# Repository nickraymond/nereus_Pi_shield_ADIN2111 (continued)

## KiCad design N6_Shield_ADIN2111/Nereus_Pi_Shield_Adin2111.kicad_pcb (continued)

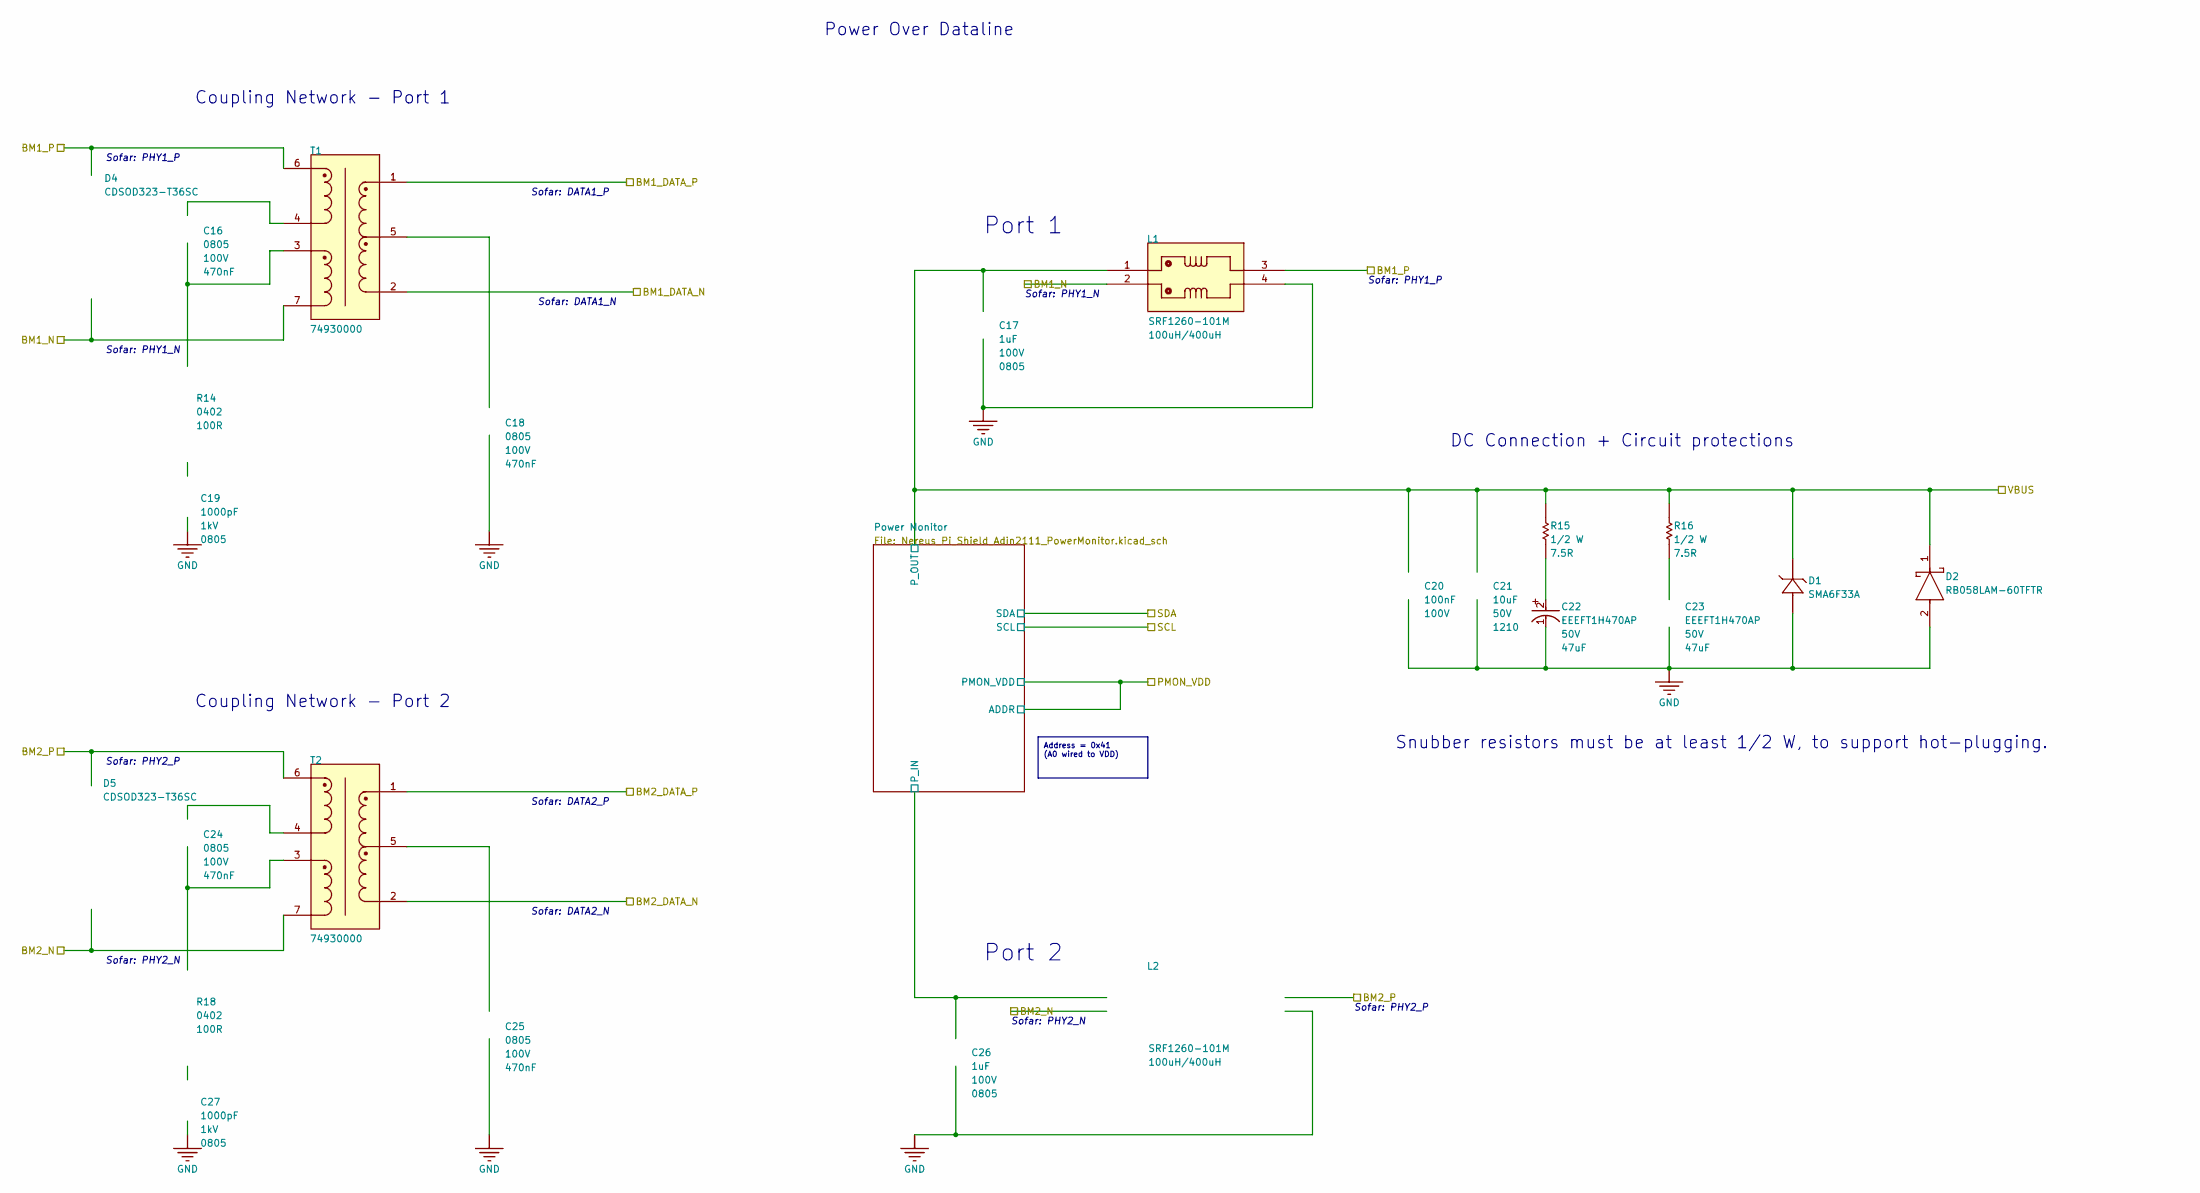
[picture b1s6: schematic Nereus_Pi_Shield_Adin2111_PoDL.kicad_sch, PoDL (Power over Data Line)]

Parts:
C16, C18, C24, C25: 08051C474KAT2A; FP-0805-L_2_01_0_2-W_1_25-MFG; TOLERANCE 10%; VOLTAGE RATING 100V
C17, C26: C2012X7S2A105K125AB; FP-C2012-125-0_2-MFG; VOLTAGE RATING (DC) 100V; VOLTAGE 100V
C19, C27: C0805C102MDRACTU; CAPC2013X145X50LL20T25; VOLTAGE 1kV; PART NUMBER C0805C102MDRACTU
C20: GRM188R72A104KA35D; FP-GRM188-0_1-e0_2_0_5-IPC_B; VOLTAGE RATING (DC) 100V; VOLTAGE 100V
C21: CL32B106KBJNNNE; FP-CL32-IPC_C; VOLTAGE RATING (DC) 50V; VOLTAGE RATING 50V
C22, C23: EEEFT1H470AP; FP-FTD-MFG; VOLTAGE 50V; TOLERANCE 20%
D1: SMA6F33A; SMA6F33A-Footprint-1; VOLTAGE - CLAMPING (MAX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 53.1V; VOLTAGE - REVERSE STAND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 33V; MANUFACTURERPARTNUMBER1 SMA6F33A-M3/H
D2: RB058LAM-60TFTR; FP-PMDTM-MFG
D4, D5: CDSOD323-T36SC; FP-SOD-323-MFG; BREAKDOWN VOLTAGE 40V; CLAMPING VOLTAGE 75V; MANUFACTURER PART NUMBER CDSOD323-T36SC; DIGIKEY DESCRIPTION TVS DIODE 36V 75V SOD323
L1, L2: SRF1260-101M; SRF1260-101M-Footprint-1
R14, R18: RR0510P-101-D; FP-RR0510-IPC_B; RESISTANCE TOLERANCE 0.5%; POWER RATING 63mW
R15, R16: CRCW08057R50FKEAHP; CRCW08057R50FKEAHP-Footprint-1; MANUFACTURERPARTNUMBER CRCW08057R50FKEAHP
T1, T2: 74930000; FP-74930000-MFG

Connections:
/Top-Level Schematic/BM1_DATA_N: T1.2; also elsewhere on the board
/Top-Level Schematic/BM1_DATA_P: T1.1; also elsewhere on the board
/Top-Level Schematic/BM1_N: D4.2, L1.2, T1.7; also elsewhere on the board
/Top-Level Schematic/BM1_P: D4.1, L1.3, T1.6; also elsewhere on the board
/Top-Level Schematic/BM2_DATA_N: T2.2; also elsewhere on the board
/Top-Level Schematic/BM2_DATA_P: T2.1; also elsewhere on the board
/Top-Level Schematic/BM2_N: D5.2, L2.2, T2.7; also elsewhere on the board
/Top-Level Schematic/BM2_P: D5.1, L2.3, T2.6; also elsewhere on the board
/Top-Level Schematic/PoDL/Power Monitor/P_IN: C26.1, L2.1; also elsewhere on the board
GND: C17.2, C18.1, C19.1, C20.2, C21.2, C22.1 (C), C23.1 (C), C25.1, C26.2, C27.1, D1.1 (ANODE), D2.2 (A), L1.4, L2.4; also elsewhere on the board
unnamed: C16.1, R14.1, T1.3
unnamed: C16.2, T1.4
unnamed: C18.2, T1.5
unnamed: C19.2, R14.2
unnamed: C22.2 (A), R15.1
unnamed: C23.2 (A), R16.1
unnamed: C24.1, R18.1, T2.3
unnamed: C24.2, T2.4
unnamed: C25.2, T2.5
unnamed: C27.2, R18.2
VBUS: C17.1, C20.1, C21.1, D1.2 (CATHODE), D2.1 (C), L1.1, R15.2, R16.2; also elsewhere on the board

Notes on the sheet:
Coupling Network - Port 2
DC Connection + Circuit protections
Sofar: PHY1_P
Sofar: PHY1_N
Sofar: DATA1_P
Snubber resistors must be at least 1/2 W, to support hot-plugging.
Port 2
Coupling Network - Port 1
Sofar: PHY2_P
Sofar: DATA1_N
Port 1
Sofar: DATA2_N
Sofar: DATA2_P
Sofar: PHY2_N
Address = 0x41 (A0 wired to VDD)
Power Over Dataline

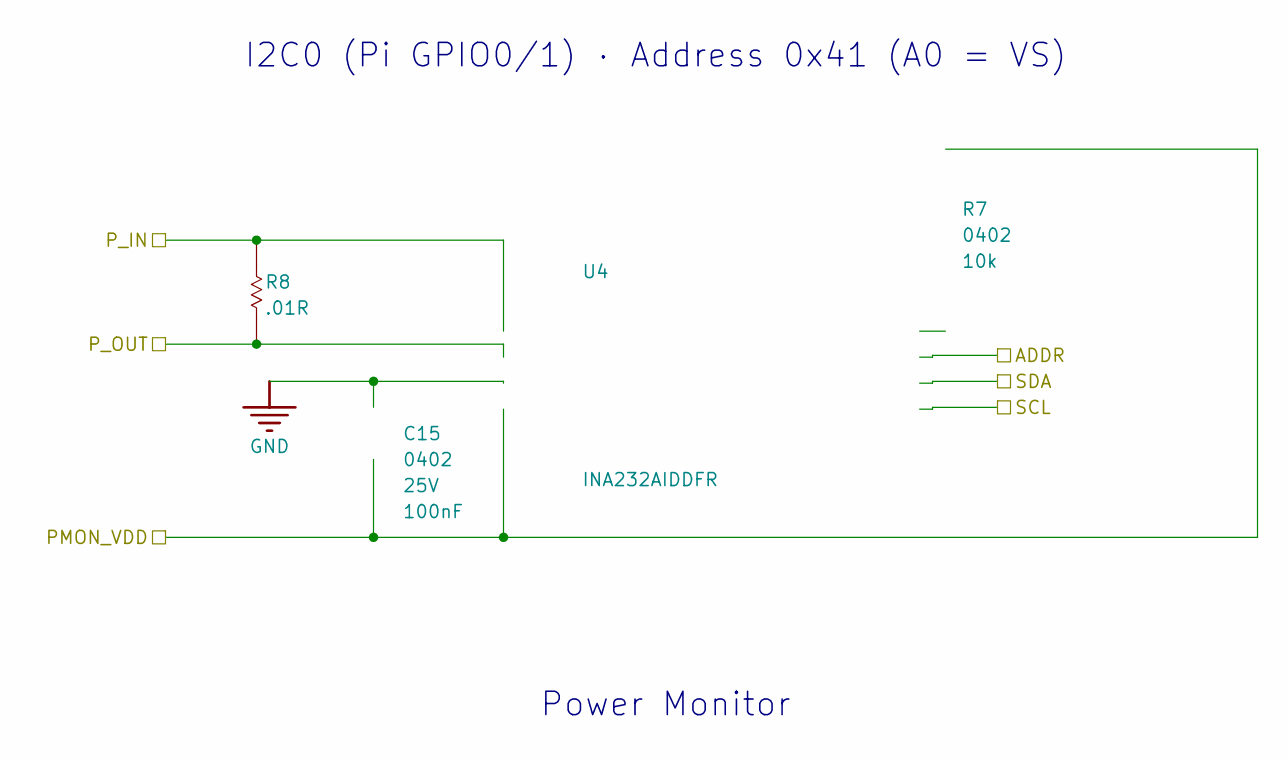
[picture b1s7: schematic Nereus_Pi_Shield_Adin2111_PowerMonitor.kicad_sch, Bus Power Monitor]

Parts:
C15: CL05A104KA5NNNC; FP-CL278-IPC_C; VOLTAGE 25V; VOLTAGE RATING 25V
R7: RC0402JR-0710KL; FP-RC0402-0_4-IPC_C; RESISTANCE TOLERANCE 5%; POWER RATING 62.5mW
R8: UR73D1JTTD10L0F; RESC1608X60X55ML20T10; MANUFACTURERPARTNUMBER UR73D1JTTD10L0F
U4: INA232AIDDFR; INA232AIDDFR-Footprint-1

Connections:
3V3: C15.2, R7.1, U4.4 (VS), U4.7 (A0); also elsewhere on the board
/Top-Level Schematic/I2C0_SCL: U4.5 (SCL); also elsewhere on the board
/Top-Level Schematic/I2C0_SDA: U4.6 (SDA); also elsewhere on the board
/Top-Level Schematic/PoDL/Power Monitor/P_IN: R8.2, U4.1 (IN+); also elsewhere on the board
GND: C15.1, U4.3 (GND); also elsewhere on the board
unnamed: R7.2, U4.8 (ALERT)
VBUS: R8.1, U4.2 (IN-); also elsewhere on the board

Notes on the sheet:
I2C0 (Pi GPIO0/1) · Address 0x41 (A0 = VS)
Power Monitor

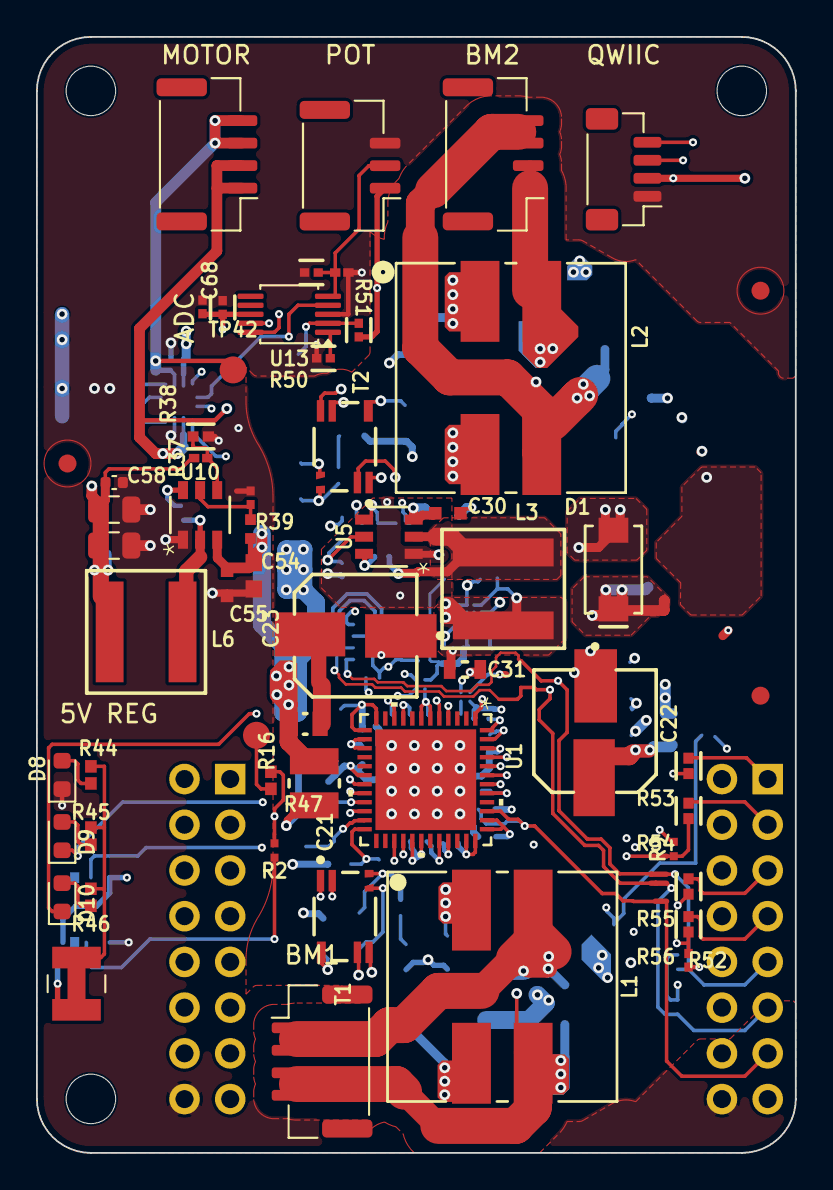
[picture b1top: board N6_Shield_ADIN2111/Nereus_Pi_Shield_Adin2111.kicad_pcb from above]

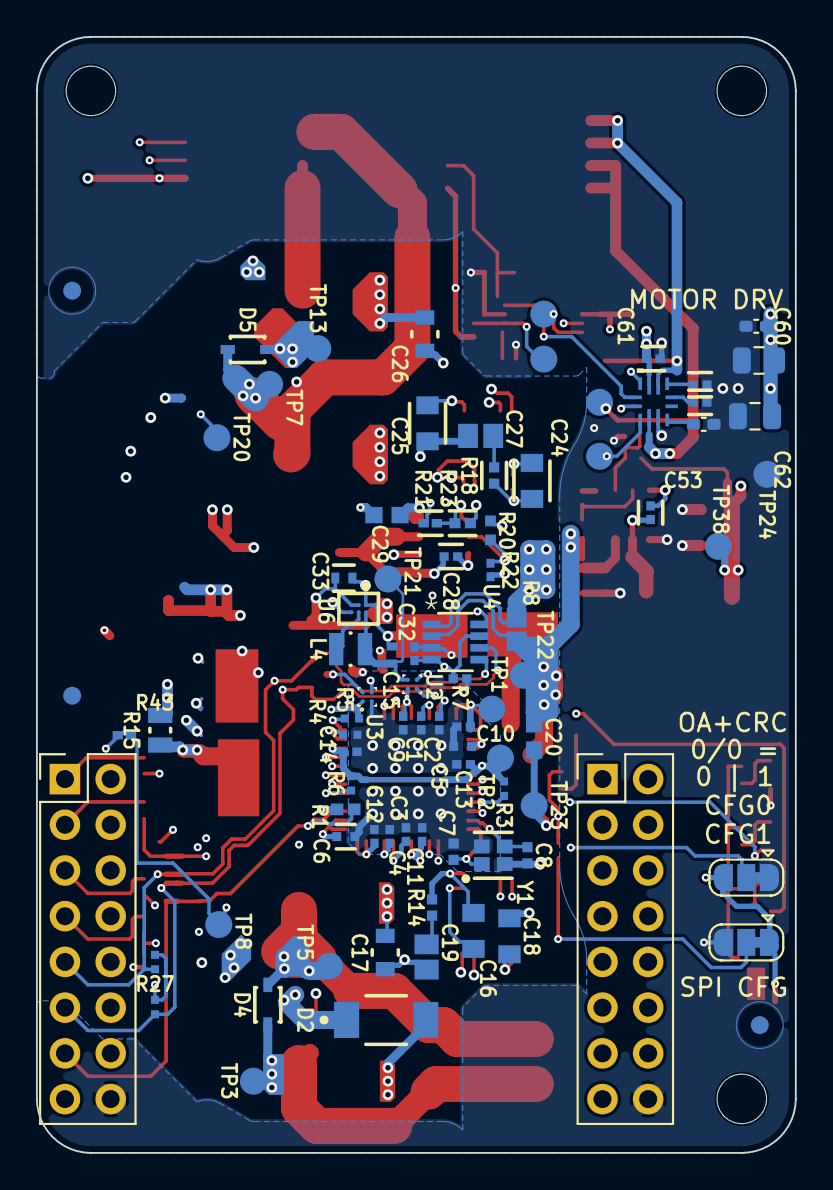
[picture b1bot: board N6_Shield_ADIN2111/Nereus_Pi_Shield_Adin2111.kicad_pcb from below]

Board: 6 copper layers, 42.2 x 62.0 mm, 147 parts (87 on the bottom side), 83 nets.

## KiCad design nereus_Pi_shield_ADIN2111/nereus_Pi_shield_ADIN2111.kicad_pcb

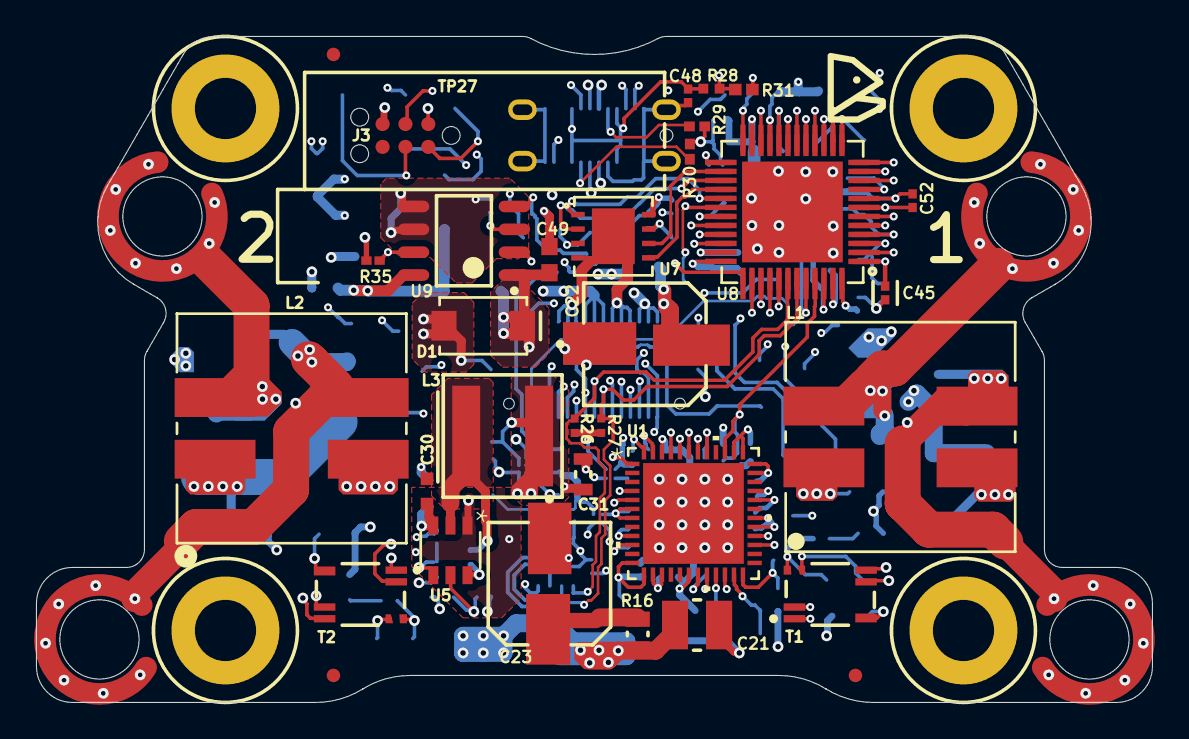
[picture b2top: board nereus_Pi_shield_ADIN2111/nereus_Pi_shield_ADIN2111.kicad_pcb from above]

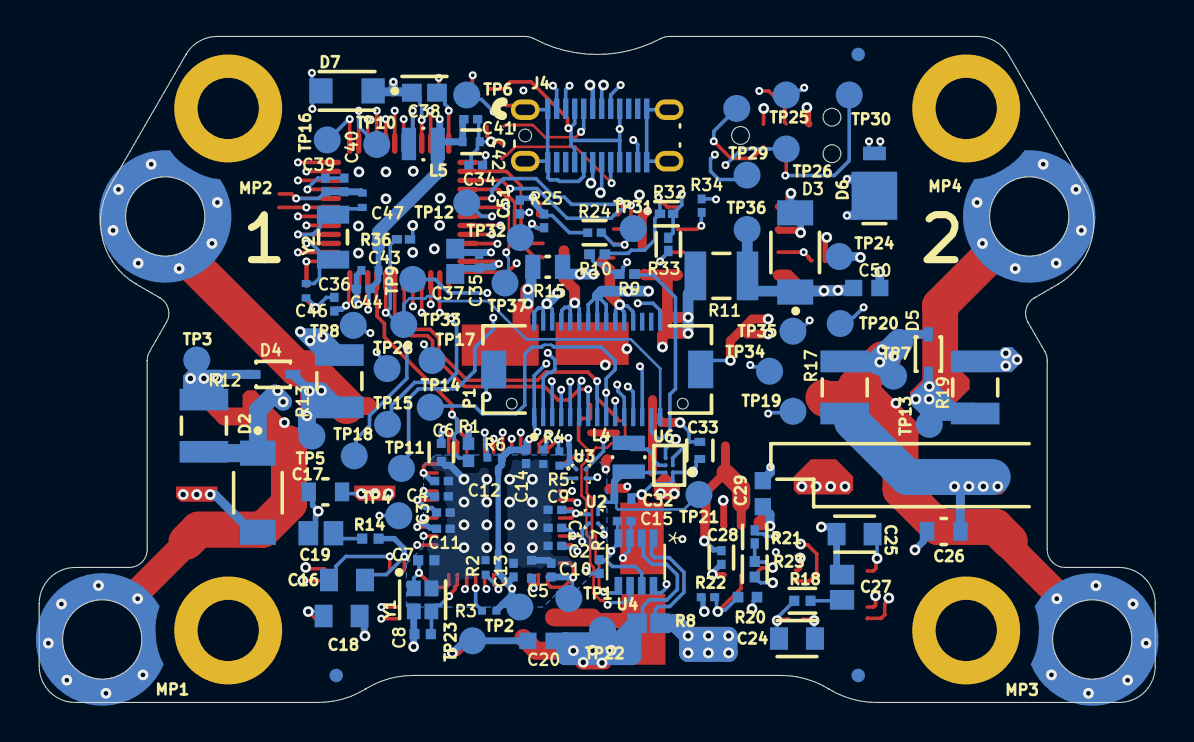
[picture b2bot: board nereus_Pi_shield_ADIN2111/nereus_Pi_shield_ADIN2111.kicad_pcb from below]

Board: 6 copper layers, 62.0 x 37.0 mm, 167 parts (131 on the bottom side), 92 nets.

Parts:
C1, C3, C9, C10, C11, C12, C13, C14, C15, C28, C34, C35, C36, C39, C41, C44, C45, C48, C51, C52: CL05A104KA5NNNC; FP-CL278-IPC_C
C2, C4, C40: CL05A105KP5NNNC; FP-CL511-IPC_C
C5, C6: CC0402KRX5R6BB684; FP-CC0402-MFG
C7, C8: CC0402JRNPO9BN150; FP-CC0402-0_55-IPC_B
C16, C18, C24, C25: 08051C474KAT2A; FP-0805-L_2_01_0_2-W_1_25-MFG
C17, C26: C2012X7S2A105K125AB; FP-C2012-125-0_2-MFG
C19, C27: C0805C102MDRACTU; CAPC2013X145X50LL20T25
C20, C29, C49, C50: GRM188R72A104KA35D; FP-GRM188-0_1-e0_2_0_5-IPC_B
C21: CL32B106KBJNNNE; FP-CL32-IPC_C
C22, C23: EEEFT1H470AP; FP-FTD-MFG
C30: UMK107BBJ225KA-T; FP-0603-L_1_6_0_2-W_0_8_0-MFG
C31: C1608X5R0J226M080AC; CAPC1608X100X20ML10
C32: GRJ155R60J106ME11D; FP-GRJ155-0_2-MFG
C33: GRM155R60J475ME87D; FP-GRM155-0_15-MFG
C37, C38: GRM188D71A106MA73D; FP-GRM188-0_2-IPC_B
C42, C43: LMK105BJ225KV-F; FP-0402-L_1_0_0_05-W_0_5-MFG
C46, C47: CGA2B2C0G1H050C050BA; FP-CGA2B-MFG
D1: SMA6F33A; SMA6F33A-Footprint-1
D2, D3: RB058LAM-60TFTR; FP-PMDTM-MFG
D4, D5: CDSOD323-T36SC; FP-SOD-323-MFG
D6: SS3P3-M3/84A; SS3P3-M3_84A-Footprint-1
D7: SMF3.3; FP-SMF3_3-MFG
FID1, FID2, FID3, FID4, FID5, FID6: FIDUCIAL; FIDUCIAL_075MM
J3: TC2030-FP-sofar; TC2030-FP-Footprint-1
J4: USB4160-03-0070-C; USB4160-03-0070-C-Footprint-1
L1, L2: SRF1260-101M; SRF1260-101M-Footprint-1
L3: PA5432.822NLT; FP-PA5432_472NLT-MFG
L4: DFE201612E-2R2M=P2; FP-DFE201612C-MFG
L5: LQM2MPN2R2NG0L; FP-LQM2MPN_G0-MFG
MP1, MP2, MP3, MP4: 78614015360; 78614015360-Footprint-2
MTG1, MTG2, MTG3, MTG4: Hole_M3
P1: DF17(3.0)-30DS-0.5V(57); FP-DF17_3_0H_-30DS-0_5V_5-MFG
R1, R31: RC0402FR-071K5L; RESC1005X40X25ML05T10
R2, R3, R4, R5, R6, R26, R27: ERJ-2RKF4701X; RESC1005X40X25LL05T05
R7, R24, R25: RC0402JR-0710KL; FP-RC0402-0_4-IPC_C
R8: UR73D1JTTD10L0F; RESC1608X60X55ML20T10
R9, R10: RC0402JR-070RL; RESC1005X40X25NL05T10
R11, R12, R13, R17, R19: CRCW12100000Z0EA; FP-CRCW1210-e3-IPC_B
R14, R18: RR0510P-101-D; FP-RR0510-IPC_B
R15, R16: CRCW08057R50FKEAHP; CRCW08057R50FKEAHP-Footprint-1
R20: CRCW04021M82FKED; FP-CRCW0402-e3-MFG
R21, R32, R33, R35, R36: RMCF0402FT100K; FP-RMCF0402-IPC_C
R22: RC0402FR-07200KL; RESC1005X40X25LL05T10
R23: RC0402FR-0722K1L; FP-RC0402-0_4-IPC_B
R28: ERJ-2RKF1001X; RESC1005X40X25NL05T05
R29, R30: RC0402FR-075K1L; RESC1005X40X25NL05T10
R34: RC0402FR-07374KL; RESC1005X40X25LL05T10
T1, T2: 74930000; FP-74930000-MFG
TP1, TP2, TP3, TP4, TP5, TP6, TP7, TP8, TP9, TP10, TP11, TP12, TP13, TP14, TP15, TP16, TP17, TP18, TP19, TP20, TP21, TP22, TP23, TP24, TP25, TP26, TP27, TP28, TP29, TP30, TP31, TP32, TP33, TP34, TP35, TP36, TP37: TEST_POINT; PCB_TP_1.5mm
U1: ADIN2111BCPZ; ADIN2111BCPZ-Footprint-1
U2, U3: AP22913CN4-7; AP22913CN4-7-Footprint-1
U4: INA232AIDDFR; INA232AIDDFR-Footprint-1
U5: LMR51430YDDCR; SOT-23-THIN-6_DDC_TEX
U6: TPS62840YBGR; FP-YBG0006-MFG
U7: W25Q64JVXGIQ; W25Q64JVXGIQ-Footprint-1
U8: STM32U575CIU6Q; STM32U575CIU6Q-Footprint-2
U9: FPF2700MX; FAIR-SO-8_V
Y1: ABM11W-25.0000MHZ-6-K1Z-T3; FP-ABM11W-MFG
Y2: NX3215SA-32.768K-STD-MUS-2; FP-NX3215SA-MFG

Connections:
1V8: C32.1, L4.2, TP21.1, U2.A2, U6.A2
3V3: C15.2, C31.2, C33.1, C34.1, C35.1, C36.1, C37.1, C38.1, C39.1, C40.1, C45.1, C51.2, D6.1, D7.1, J3.1, J4.A8, L3.2, P1.2, P1.4, P1.6, R7.1, R21.1, R24.1, R25.1, R26.2, R27.2, R32.2, R33.2, R35.2, TP20.1, U3.A2, U4.4, U4.7, U6.B1, U6.C1, U7.8, U8.1, U8.9, U8.21, U8.25, U8.36, U8.48
3V3_Buck_SW: C28.1, L3.1, U5.2
3V3_FB: R21.2, R23.1, U5.4
3V3_UVLO: R20.1, R22.2, U5.5
5VUSB: C48.1, J4.A4, J4.A9, J4.B4, J4.B9, R28.2, TP25.1
ADC1_IN16: R9.2, R10.2, TP19.1, U8.19
ADIN_AVDD: C9.1, C10.1, C11.1, C12.1, TP1.1, U1.6, U1.7, U1.12, U1.13, U1.29, U1.30, U1.35, U1.36, U2.A1
ADIN_CLK25_REF: U1.1, U1.22
ADIN_INT: R1.1, U1.39, U8.45
ADIN_MISO: U1.43, U8.40
ADIN_MOSI: U1.42, U8.41
ADIN_NSS: U1.45, U8.38
ADIN_PWR: TP8.1, U2.B2, U3.B2, U8.6
ADIN_RST: U1.20, U8.10
ADIN_SCK: U1.44, U8.39
ADIN_VDDIO: C13.1, C14.1, R1.2, R3.2, R5.2, R6.2, TP2.1, U1.18, U1.46, U3.A1
BM1_DATA_N: T1.2, U1.27
BM1_DATA_P: T1.1, U1.28
BM1_N: D4.2, L1.2, R13.2, T1.7, TP5.1
BM1_P: D4.1, L1.3, R12.1, T1.6, TP3.1
BM2_DATA_N: T2.2, U1.4
BM2_DATA_P: T2.1, U1.5
BM2_N: D5.2, L2.2, R19.2, T2.7, TP13.1
BM2_P: D5.1, L2.3, R17.1, T2.6, TP7.1
BM_CS: P1.7, TP10.1, U8.14
BM_INT: P1.9, TP11.1, U8.18
BM_MISO: P1.1, TP4.1, U8.16
BM_MOSI-TX3: P1.3, TP6.1, U8.17
BM_SCK-RX3: P1.5, TP9.1, U8.15
BOOT: P1.29, R36.2, TP33.1, U8.44
DVDD1_1P1: C6.1, U1.37, U1.38
DVDD2_1P1: C5.1, U1.14, U1.15
FLASH_CS: U7.1, U8.29
FLASH_MISO: U7.2, U8.27
FLASH_MOSI: U7.5, U8.28
FLASH_SCK: U7.6, U8.26
GND: C1.2, C2.2, C3.2, C4.2, C5.2, C6.2, C7.2, C8.2, C9.2, C10.2, C11.2, C12.2, C13.2, C14.2, C15.1, C17.2, C18.1, C19.1, C20.2, C21.2, C22.1, C23.1, C25.1, C26.2, C27.1, C29.2, C30.2, C31.1, C32.2, C33.2, C34.2, C35.2, C36.2, C37.2, C38.2, C39.2, C40.2, C41.2, C42.2, C43.2, C44.2, C45.2, C46.2, C47.2, C48.2, C49.2, C50.2, C51.1, C52.2, D1.1, D2.2, D3.2, D6.2, D7.2, J3.5, J4.A1, J4.A12, J4.B1, J4.B8, J4.B12, J4.Shell, L1.4, L2.4, P1.8, P1.10, P1.12, P1.20, P1.22, P1.24, P1.31, P1.32, R2.2, R4.2, R13.1, R19.1, R22.1, R23.2, R29.1, R30.1, R31.1, R34.1, R36.1, TP23.1, TP24.1, U1.49, U2.B1, U3.B1, U4.3, U5.1, U6.A1, U6.C2, U7.4, U7.9, U8.8, U8.22, U8.24, U8.35, U8.47, U8.49, U9.5, U9.6, Y1.2, Y1.4
GPIO1: P1.17, TP14.1, U8.5
GPIO2: P1.19, TP15.1, U8.2
I2C1_SCL: P1.15, R26.1, U4.5, U8.42
I2C1_SDA: P1.13, R27.1, U4.6, U8.43
I2C_MUX_RST: P1.25, TP18.1, U8.11
IOEXP_INT: P1.11, TP12.1, U8.31
ISET: R34.2, U9.3
LPUART1_RX: P1.21, TP16.1, U8.13
LPUART1_TX: P1.23, TP17.1, U8.12
MCU_RESET: C52.1, J3.3, J4.B2, P1.30, TP28.1, U8.7
MZ_ADC_EXTRA: P1.27, R9.1
NetC1_1: C1.1, U1.9
NetC2_1: C2.1, U1.10
NetC3_1: C3.1, U1.32
NetC4_1: C4.1, U1.33
NetC7_1: C7.1, U1.24, Y1.1
NetC8_1: C8.1, U1.23, Y1.3
NetC16_1: C16.1, R14.1, T1.3
NetC16_2: C16.2, T1.4
NetC18_2: C18.2, T1.5
NetC19_2: C19.2, R14.2
NetC22_2: C22.2, R15.1
NetC23_2: C23.2, R16.1
NetC24_1: C24.1, R18.1, T2.3
NetC24_2: C24.2, T2.4
NetC25_2: C25.2, T2.5
NetC27_2: C27.2, R18.2
NetC28_2: C28.2, U5.6
NetL4_1: L4.1, U6.B2
NetR2_1: R2.1, U1.19
NetR3_1: R3.1, U1.21
NetR4_1: R4.1, U1.47
NetR5_1: R5.1, U1.48
NetR6_1: R6.1, U1.41
NetR7_2: R7.2, U4.8
NetR24_2: R24.2, TP31.1, U7.3
NetR25_2: R25.2, TP32.1, U7.7
PC14-OSC32_IN: C46.1, U8.3, Y2.1
PC14-OSC32_OUT: C47.1, U8.4, Y2.2
P_IN: C26.1, L2.1, R8.2, R17.2, U4.1
SWDCLK: J3.4, J4.A3, TP30.1, U8.37
SWDIO: J3.2, J4.A2, TP27.1, U8.34
SW_FLAGB: R35.1, TP35.1, U9.7
SW_ON: R10.1, R32.1, U9.4
SW_PGOOD: R33.1, TP34.1, U9.2
USB_CC1: J4.A5, R29.2
USB_CC2: J4.B5, R30.2
USB_N: J4.A7, J4.B7, TP29.1, U8.32
USB_P: J4.A6, J4.B6, TP26.1, U8.33
VBUS: C17.1, C20.1, C21.1, C29.1, C30.1, C49.1, D1.2, D2.1, L1.1, R8.1, R11.1, R12.2, R15.2, R16.2, R20.2, TP22.1, U4.2, U5.3, U9.1
VBUS_OUT: C50.1, D3.1, P1.14, P1.16, P1.18, R11.2, TP36.1, U9.8
VDD11: C41.1, C42.1, C43.1, C44.1, L5.2, U8.23, U8.46
VLXSMPS: L5.1, U8.20
VUSB_DETECT: R28.1, R31.2, TP37.1, U8.30

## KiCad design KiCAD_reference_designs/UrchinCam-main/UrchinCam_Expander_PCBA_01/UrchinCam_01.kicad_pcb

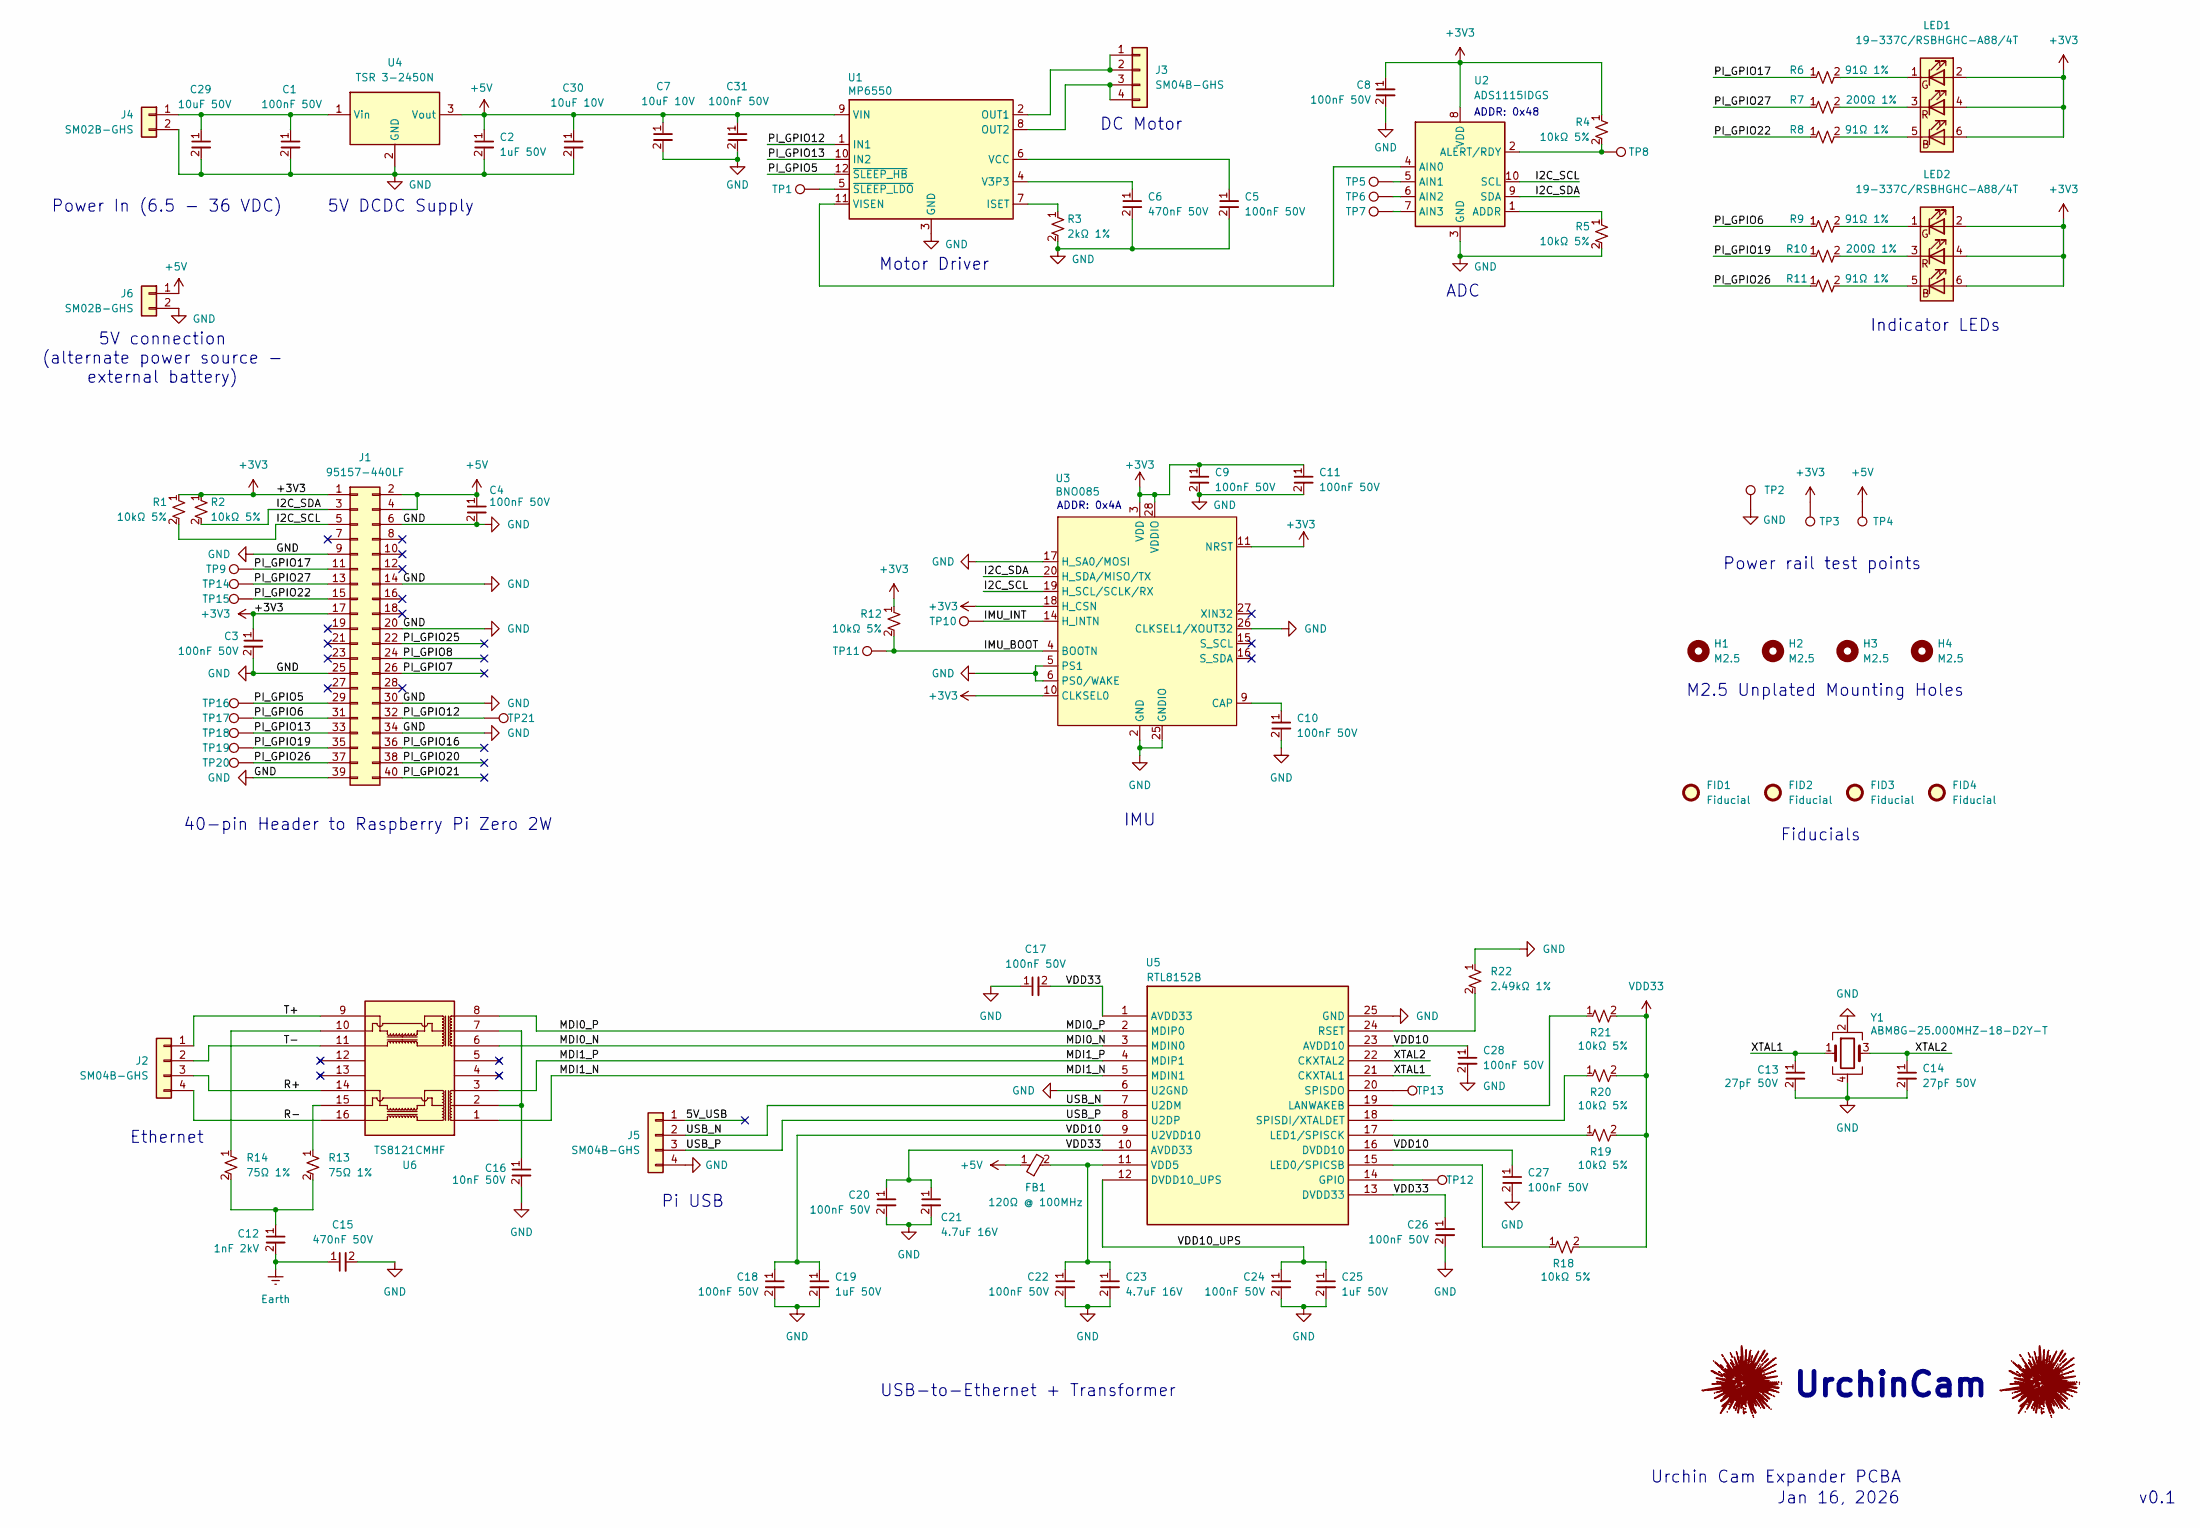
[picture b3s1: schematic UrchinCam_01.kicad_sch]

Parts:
C1, C3, C4, C5, C8, C9, C10, C11, C17, C18, C20, C22, C24, C26, C27, C28, C31: 100nF 50V; C_0402_1005Metric_Pad0.74x0.62mm_HandSolder
C2, C19, C25: 1uF 50V; C_0402_1005Metric_Pad0.74x0.62mm_HandSolder
C6, C15: 470nF 50V; C_0402_1005Metric_Pad0.74x0.62mm_HandSolder
C7, C30: 10uF 10V; C_0402_1005Metric_Pad0.74x0.62mm_HandSolder
C12: 1nF 2kV; C_1206_3216Metric_Pad1.33x1.80mm_HandSolder
C13, C14: 27pF 50V; C_0402_1005Metric_Pad0.74x0.62mm_HandSolder
C16: 10nF 50V; C_0402_1005Metric_Pad0.74x0.62mm_HandSolder
C21, C23: 4.7uF 16V; C_0402_1005Metric_Pad0.74x0.62mm_HandSolder
C29: 10uF 50V; C_0805_2012Metric_Pad1.18x1.45mm_HandSolder
FB1: 120Ω @ 100MHz; R_0402_1005Metric_Pad0.72x0.64mm_HandSolder
FID1, FID2, FID3, FID4: Fiducial; Fiducial_0.5mm_Mask1mm
H1, H2, H3, H4: M2.5; M2.5_Mounting_Hole_2.9mm_unplated
J1: 95157-440LF; Amphenol_95157-440LF_2x20_P2.54mm_Vertical
J2, J3, J5: SM04B-GHS; JST_GH_SM04B-GHS-TB_1x04-1MP_P1.25mm_Horizontal
J4, J6: SM02B-GHS; JST_GH_SM02B-GHS-TB_1x02-1MP_P1.25mm_Horizontal
LED1, LED2: 19-337C/RSBHGHC-A88/4T; 19-337C RSBHGHC-A88 4T
R1, R2, R4, R5, R12, R18, R19, R20, R21: 10kΩ 5%; R_0402_1005Metric_Pad0.72x0.64mm_HandSolder
R3: 2kΩ 1%; R_0402_1005Metric_Pad0.72x0.64mm_HandSolder
R6, R8, R9, R11: 91Ω 1%; R_0603_1608Metric_Pad0.98x0.95mm_HandSolder
R7, R10: 200Ω 1%; R_0603_1608Metric_Pad0.98x0.95mm_HandSolder
R13, R14: 75Ω 1%; R_0402_1005Metric_Pad0.72x0.64mm_HandSolder
R22: 2.49kΩ 1%; R_0402_1005Metric_Pad0.72x0.64mm_HandSolder
TP1, TP2, TP3, TP4, TP5, TP6, TP7, TP8, TP9, TP10, TP11, TP12, TP13, TP14, TP15, TP16, TP17, TP18, TP19, TP20, TP21: TestPoint; TestPoint_Pad_D1.5mm
U1: MP6550; MP6550GG
U2: ADS1115IDGS; TSSOP-10_3x3mm_P0.5mm
U3: BNO085; LGA-28_5.2x3.8mm_P0.5mm
U4: TSR 3-2450N; Traco_TSR 3-2450N
U5: RTL8152B
U6: TS8121CMHF; TS8121CM HF
Y1: ABM8G-25.000MHZ-18-D2Y-T; Crystal_SMD_3225-4Pin_3.2x2.5mm

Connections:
+3V3: C3.1, C8.1, C9.1, C11.1, J1.1, J1.17, LED1.2 (GA), LED1.4 (RA), LED1.6 (BA), LED2.2 (GA), LED2.4 (RA), LED2.6 (BA), R1.1, R2.1, R4.1, R12.1, TP3.1, U2.8 (VDD), U3.3 (VDD), U3.10 (CLKSEL0), U3.11 (NRST), U3.18 (H_CSN), U3.28 (VDDIO)
+5V: C2.1, C4.1, C7.1, C30.1, C31.1, FB1.1, J1.2, J1.4, J6.1, TP4.1, U1.9 (VIN), U4.3 (Vout)
/5V_USB: J5.1
/I2C_SCL: J1.5, R1.2, U2.10 (SCL), U3.19 (H_SCL/SCLK/RX)
/I2C_SDA: J1.3, R2.2, U2.9 (SDA), U3.20 (H_SDA/MISO/TX)
/IMU_BOOT: R12.2, TP11.1, U3.4 (BOOTN)
/IMU_INT: TP10.1, U3.14 (H_INTN)
/MDI0_N: U5.3 (MDIN0), U6.6
/MDI0_P: U5.2 (MDIP0), U6.8
/MDI1_N: U5.5 (MDIN1), U6.1
/MDI1_P: U5.4 (MDIP1), U6.3
/PI_GPIO5: J1.29, TP16.1, U1.12 (~SLEEP_HB)
/PI_GPIO6: J1.31, R9.1, TP17.1
/PI_GPIO7: J1.26
/PI_GPIO8: J1.24
/PI_GPIO12: J1.32, TP21.1, U1.1 (IN1)
/PI_GPIO13: J1.33, TP18.1, U1.10 (IN2)
/PI_GPIO16: J1.36
/PI_GPIO17: J1.11, R6.1, TP9.1
/PI_GPIO19: J1.35, R10.1, TP19.1
/PI_GPIO20: J1.38
/PI_GPIO21: J1.40
/PI_GPIO22: J1.15, R8.1, TP15.1
/PI_GPIO25: J1.22
/PI_GPIO26: J1.37, R11.1, TP20.1
/PI_GPIO27: J1.13, R7.1, TP14.1
/R+: J2.3, U6.14
/R-: J2.4, U6.16
/T+: J2.1, U6.9
/T-: J2.2, U6.11
/USB_N: J5.2, U5.7 (U2DM)
/USB_P: J5.3, U5.8 (U2DP)
/VDD10: C18.1, C19.1, C27.1, C28.1, U5.9 (U2VDD10), U5.16 (DVDD10), U5.23 (AVDD10)
/VDD10_UPS: C24.1, C25.1, U5.12 (DVDD10_UPS)
/XTAL1: C13.1, U5.21 (CKXTAL1), Y1.1
/XTAL2: C14.1, U5.22 (CKXTAL2), Y1.3
Earth: C12.2, C15.1
GND: C1.2, C2.2, C3.2, C4.2, C5.2, C6.2, C7.2, C8.2, C9.2, C10.2, C11.2, C13.2, C14.2, C15.2, C16.2, C17.1, C18.2, C19.2, C20.2, C21.2, C22.2, C23.2, C24.2, C25.2, C26.2, C27.2, C28.2, C29.2, C30.2, C31.2, J1.6, J1.9, J1.14, J1.20, J1.25, J1.30, J1.34, J1.39, J4.2, J5.4, J6.2, R3.2, R5.2, R22.1, TP2.1, U1.3 (GND), U2.3 (GND), U3.2 (GND), U3.5 (PS1), U3.6 (PS0/WAKE), U3.17 (H_SA0/MOSI), U3.25 (GNDIO), U3.26 (CLKSEL1/XOUT32), U4.2 (GND), U5.6 (U2GND), U5.25 (GND), Y1.2, Y1.4
unnamed: C12.1, R13.2, R14.2
unnamed: C16.1, U6.2, U6.7
unnamed: J3.1, J3.2, U1.2 (OUT1)
unnamed: J3.3, J3.4, U1.8 (OUT2)
unnamed: C1.1, C29.1, J4.1, U4.1 (Vin)
unnamed: LED1.5 (BK), R8.2
unnamed: LED1.1 (GK), R6.2
unnamed: LED1.3 (RK), R7.2
unnamed: LED2.5 (BK), R11.2
unnamed: LED2.1 (GK), R9.2
unnamed: LED2.3 (RK), R10.2
unnamed: R13.1, U6.15
unnamed: R14.1, U6.10
unnamed: R3.1, U1.7 (ISET)
unnamed: C6.1, U1.4 (V3P3)
unnamed: C5.1, U1.6 (VCC)
unnamed: U1.11 (VISEN), U2.4 (AIN0)
unnamed: TP1.1, U1.5 (~SLEEP_LDO)
unnamed: R5.1, U2.1 (ADDR)
unnamed: TP5.1, U2.5 (AIN1)
unnamed: TP6.1, U2.6 (AIN2)
unnamed: TP7.1, U2.7 (AIN3)
unnamed: R4.2, TP8.1, U2.2 (ALERT/RDY)
unnamed: C10.1, U3.9 (CAP)
unnamed: TP12.1, U5.14 (GPIO)
unnamed: R21.1, U5.19 (LANWAKEB)
unnamed: R18.1, U5.15 (LED0/SPICSB)
unnamed: R19.1, U5.17 (LED1/SPISCK)
unnamed: R22.2, U5.24 (RSET)
unnamed: R20.1, U5.18 (SPISDI/XTALDET)
unnamed: TP13.1, U5.20 (SPISDO)
unnamed: C22.1, C23.1, FB1.2, U5.11 (VDD5)
VDD33: C17.2, C20.1, C21.1, C26.1, R18.2, R19.2, R20.2, R21.2, U5.1 (AVDD33), U5.10 (AVDD33), U5.13 (DVDD33)

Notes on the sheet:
Ethernet
Power In (6.5 - 36 VDC)
Motor Driver
UrchinCam
Urchin Cam Expander PCBA
Power rail test points
DC Motor
ADC
M2.5 Unplated Mounting Holes
Pi USB
v0.1
IMU
Indicator LEDs
Jan 16, 2026
ADDR: 0x48
5V connection (alternate power source - external battery)
Fiducials
40-pin Header to Raspberry Pi Zero 2W
USB-to-Ethernet + Transformer
ADDR: 0x4A
5V DCDC Supply
